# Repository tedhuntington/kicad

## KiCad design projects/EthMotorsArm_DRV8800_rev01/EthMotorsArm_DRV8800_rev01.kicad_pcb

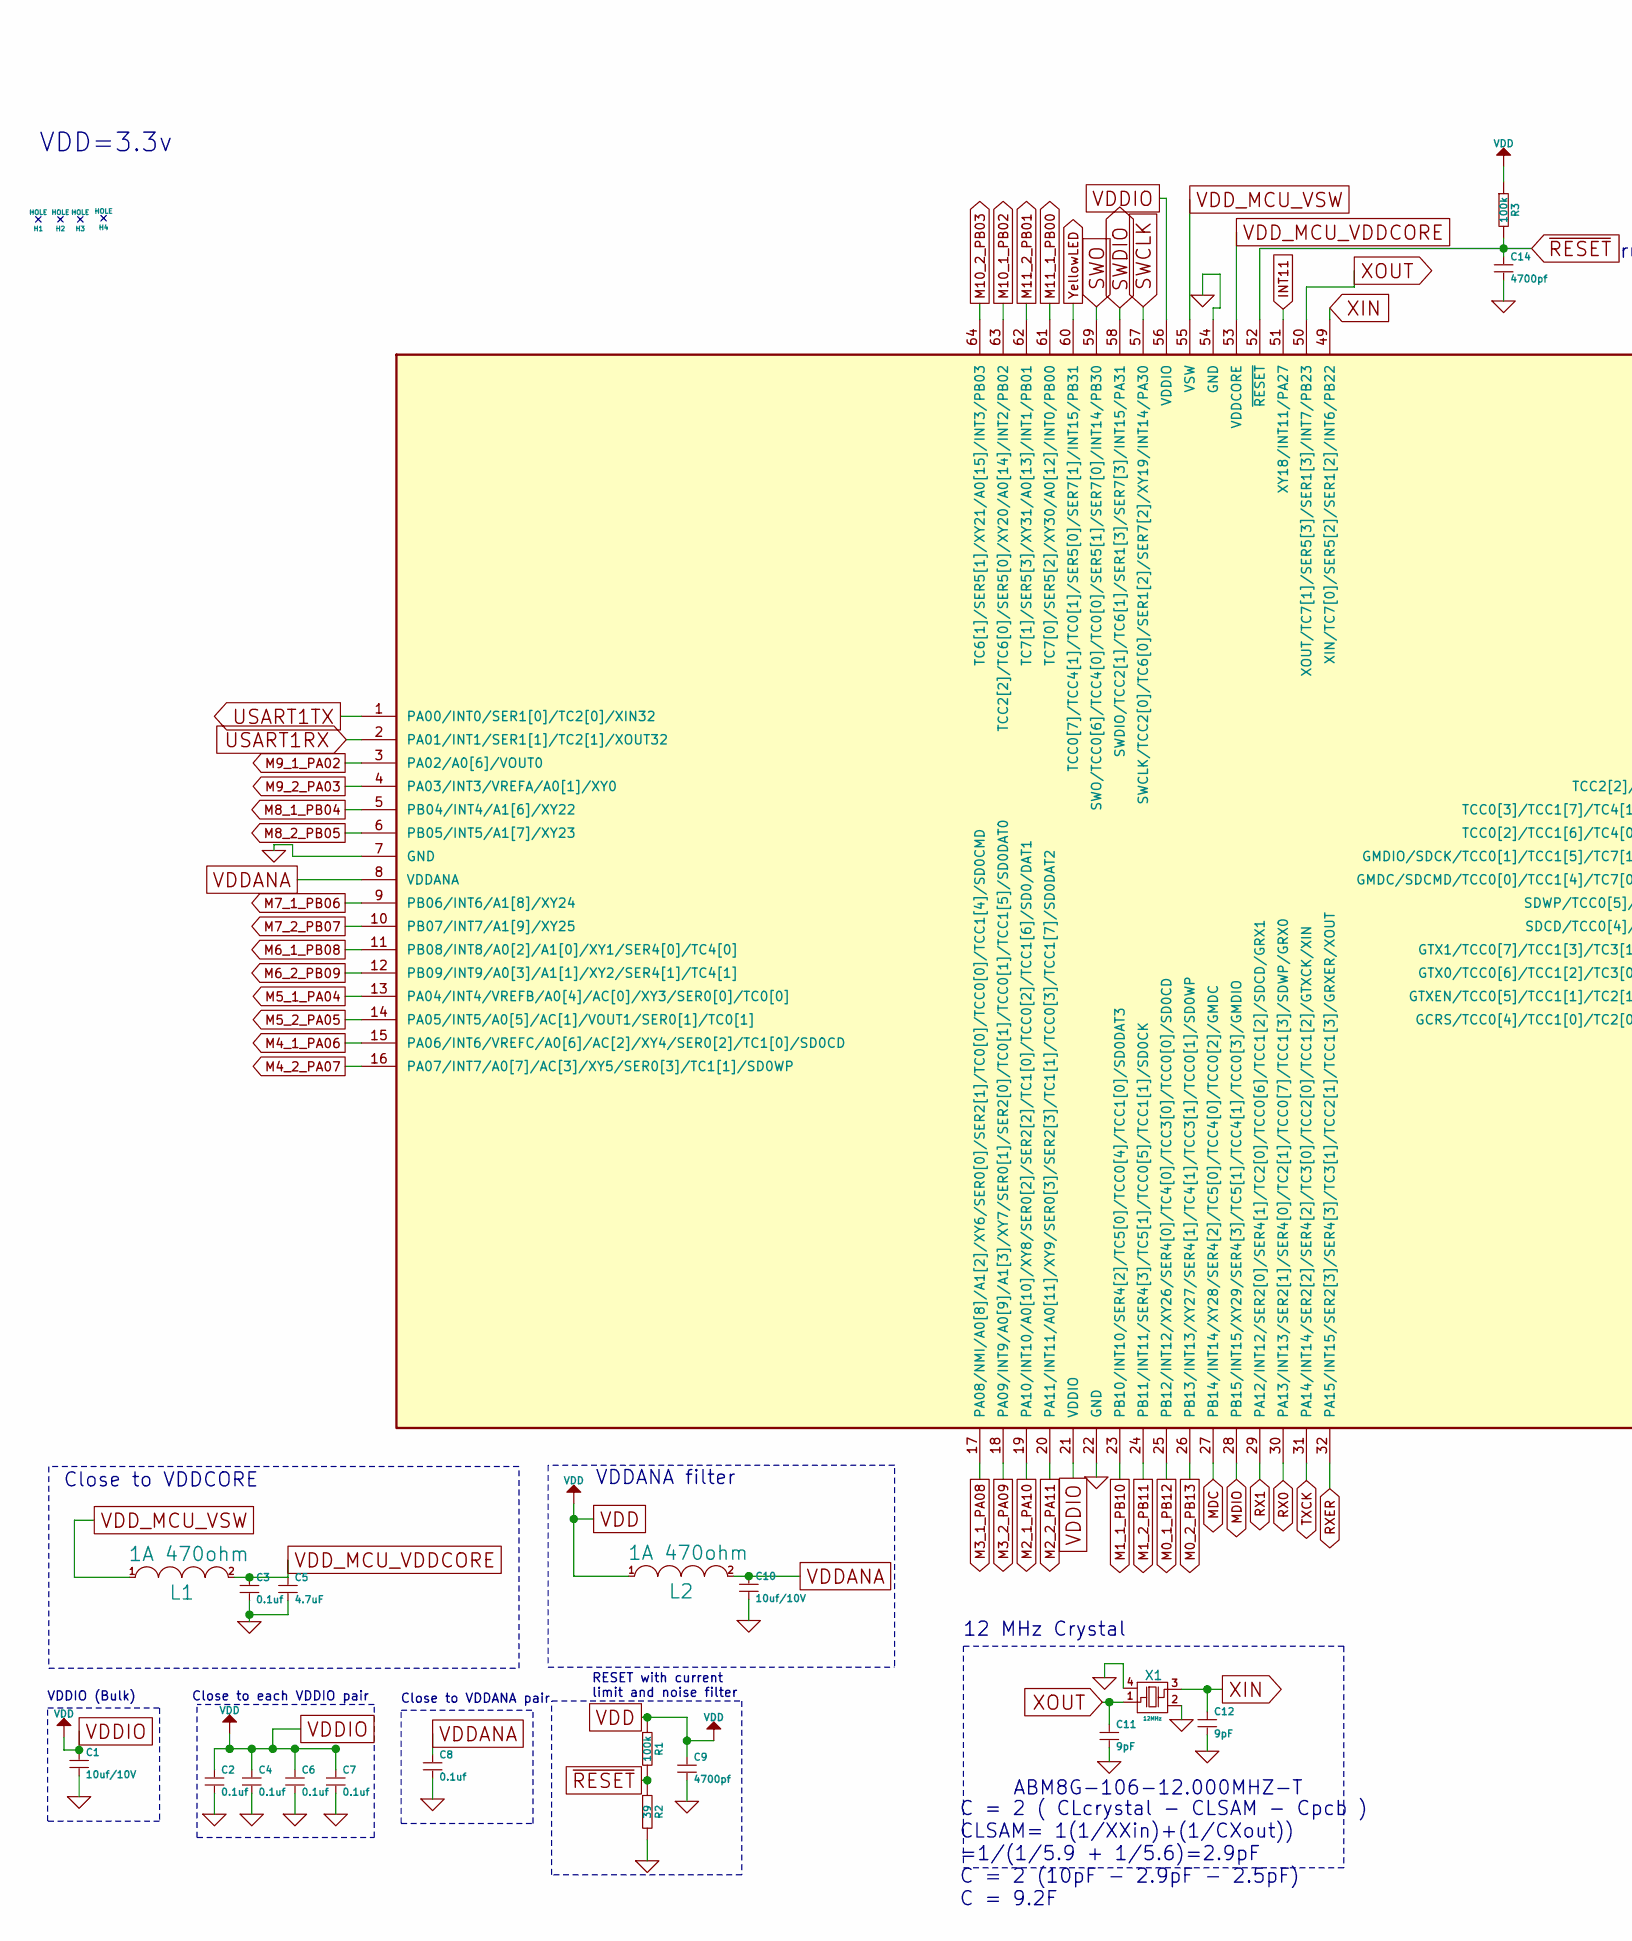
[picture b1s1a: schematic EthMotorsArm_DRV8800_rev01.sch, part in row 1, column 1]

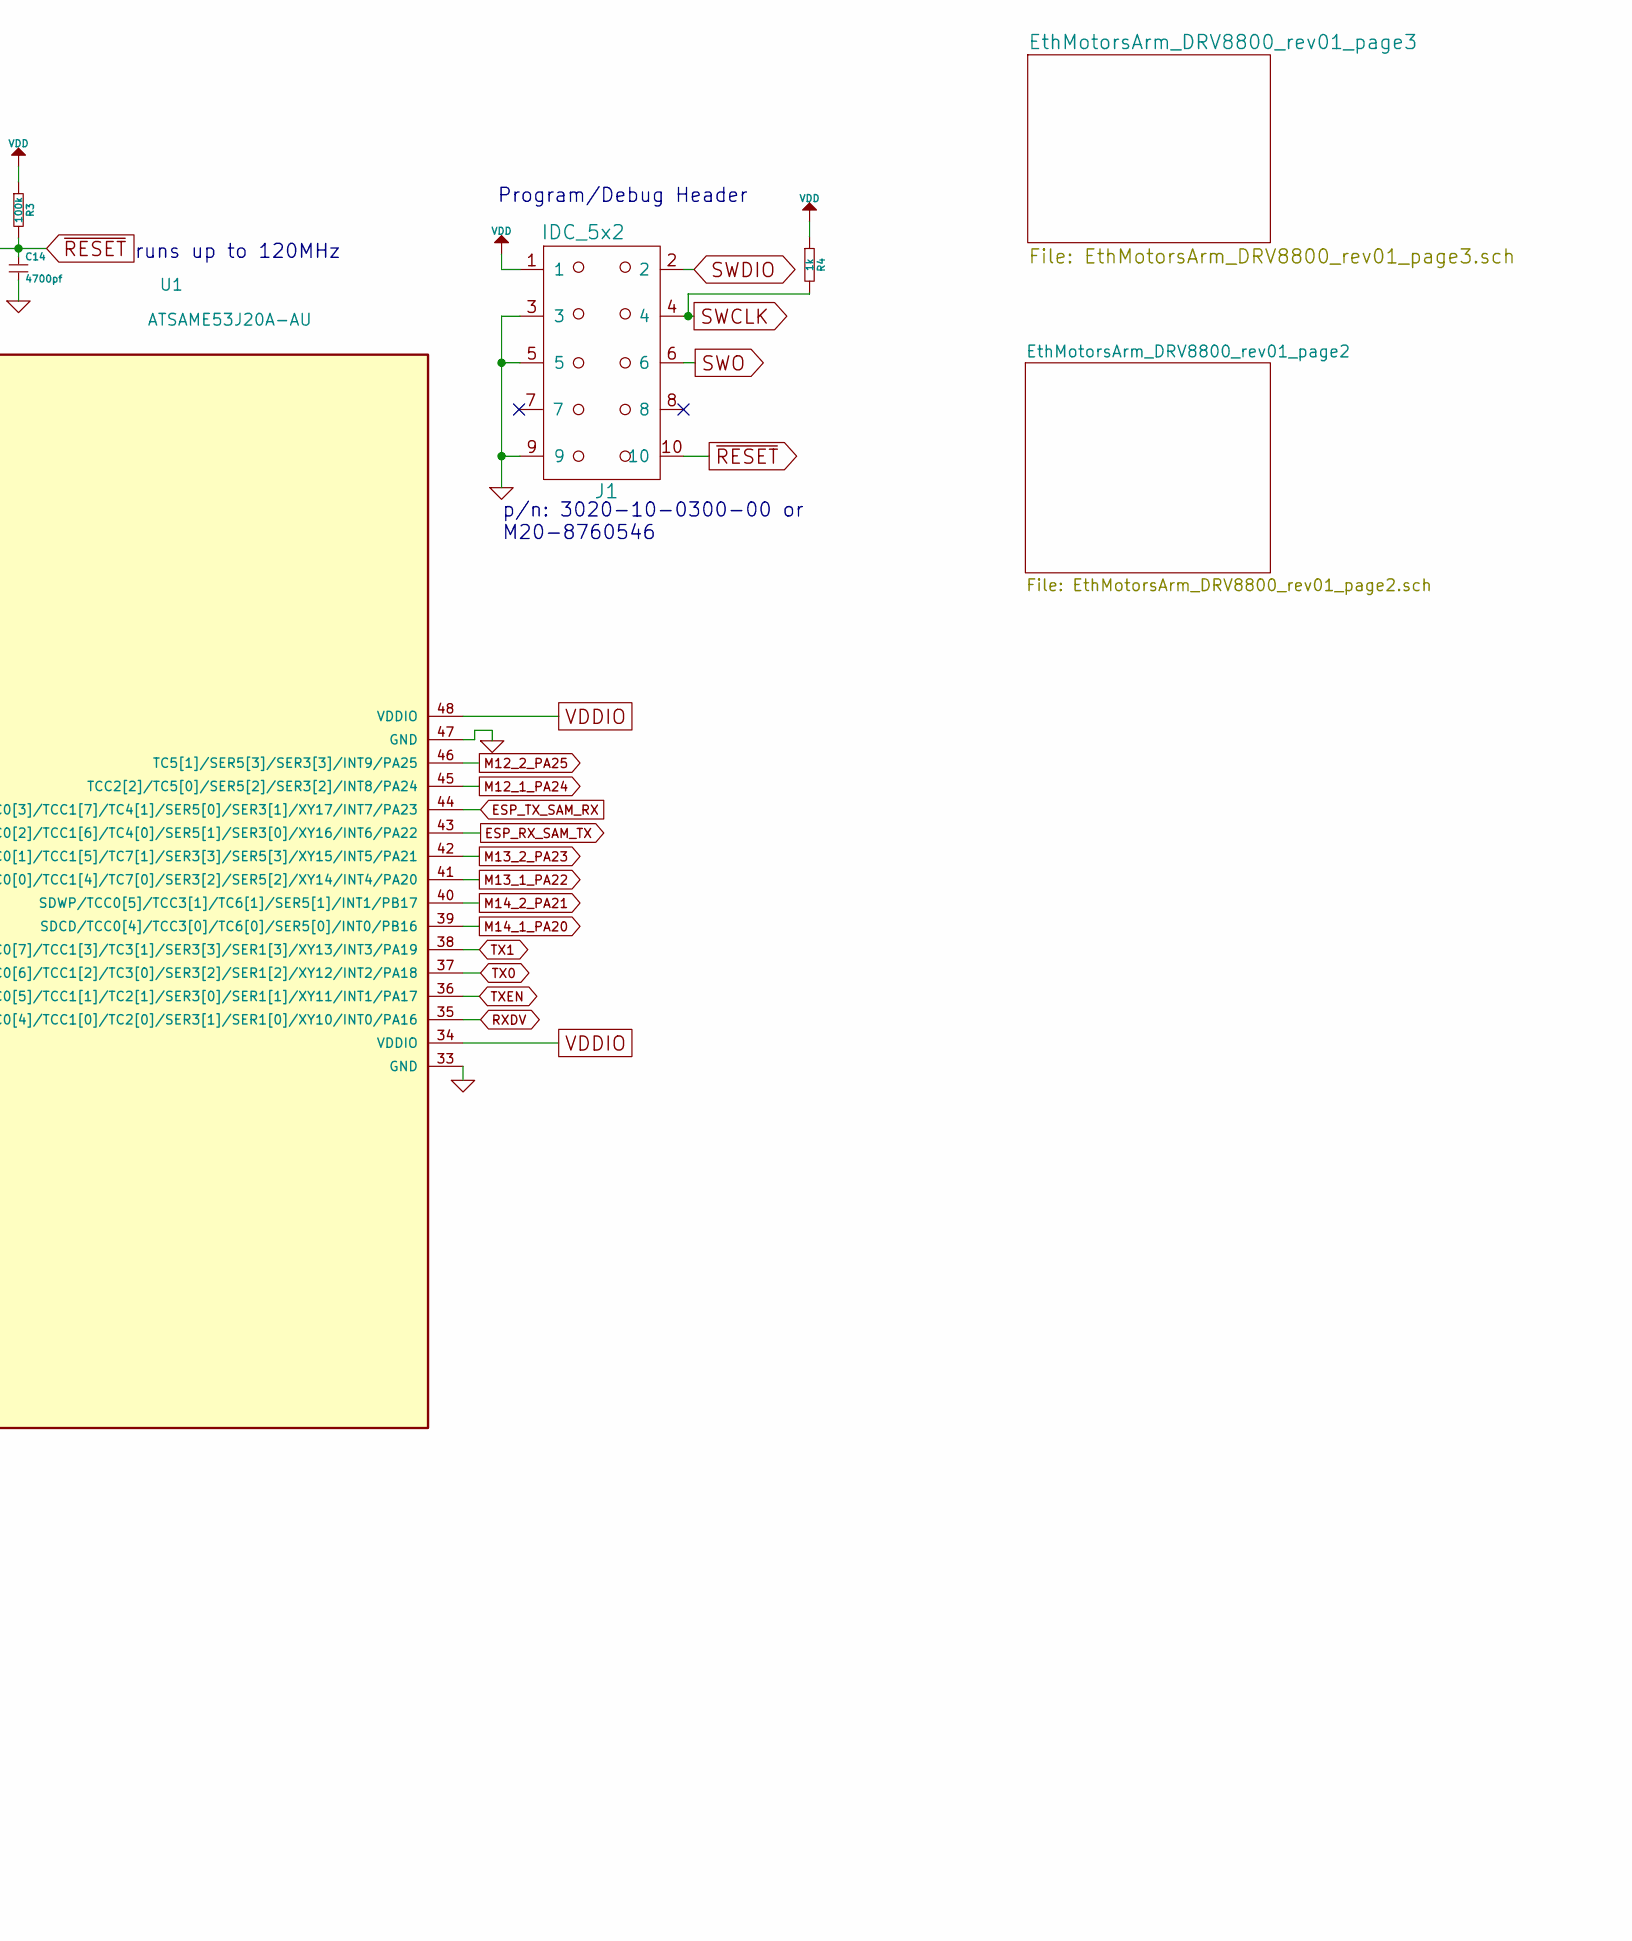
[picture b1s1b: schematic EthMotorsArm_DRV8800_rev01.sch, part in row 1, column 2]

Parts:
C1, C10: 10uf/10V; TED_SM0603_C
C2, C3, C4, C6, C7, C8: 0.1uf; TED_SM0603_C
C5: 4.7uF; TED_SM0603_C
C9, C14: 4700pf; TED_SM0603_C
C11, C12: 9pF; TED_SM0603_C
H1, H2, H3, H4: HOLE; TED_Hole_3mm
J1: IDC_5x2; TED_IDC_5x2_SMD
L1, L2: 1A 470ohm; TED_SM0603_R
R1, R3: 100k; TED_SM0603_R
R2: 39; TED_SM0603_R
R4: 1k; TED_SM0603_R
U1: ATSAME53J20A-AU; TED_TQFP64
X1: 12MHz; crystal_3.2_2.5

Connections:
ESP_RX_SAM_TX: U1.43 (TCC0[2]/TCC1[6]/TC4[0]/SER5[1]/SER3[0]/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); also elsewhere on the board
ESP_TX_SAM_RX: U1.44 (TCC0[3]/TCC1[7]/TC4[1]/SER5[0]/SER3[1]/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); also elsewhere on the board
GND: C1.2, C2.2, C3.2, C4.2, C5.2, C6.2, C7.2, C8.2, C9.2, C10.2, C11.2, C12.2, C14.2, J1.3, J1.5, J1.9, R2.2, U1.7 (GND), U1.22 (GND), U1.33 (GND), U1.47 (GND), U1.54 (GND), X1.2, X1.4; also elsewhere on the board
INT11: U1.51 (XY18/INT11/PA27); also elsewhere on the board
M0_1_PB12: U1.25 (PB12/INT12/XY26/SER4[0]/TC4[0]/TCC3[0]/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); also elsewhere on the board
M0_2_PB13: U1.26 (PB13/INT13/XY27/SER4[1]/TC4[1]/TCC3[1]/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); also elsewhere on the board
M1_1_PB10: U1.23 (PB10/INT10/SER4[2]/TC5[0]/TCC0[4]/TCC1[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); also elsewhere on the board
M1_2_PB11: U1.24 (PB11/INT11/SER4[3]/TC5[1]/TCC0[5]/TCC1[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); also elsewhere on the board
M2_1_PA10: U1.19 (PA10/INT10/A0[10]/XY8/SER0[2]/SER2[2]/T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); also elsewhere on the board
M2_2_PA11: U1.20 (PA11/INT11/A0[11]/XY9/SER0[3]/SER2[3]/T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); also elsewhere on the board
M3_1_PA08: U1.17 (PA08/NMI/A0[8]/A1[2]/XY6/SER0[0]/SER2[1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); also elsewhere on the board
M3_2_PA09: U1.18 (PA09/INT9/A0[9]/A1[3]/XY7/SER0[1]/SER2[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); also elsewhere on the board
M4_1_PA06: U1.15 (PA06/INT6/VREFC/A0[6]/AC[2]/XY4/SER0[2]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); also elsewhere on the board
M4_2_PA07: U1.16 (PA07/INT7/A0[7]/AC[3]/XY5/SER0[3]/TC1[1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); also elsewhere on the board
M5_1_PA04: U1.13 (PA04/INT4/VREFB/A0[4]/AC[0]/XY3/SER0[0]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); also elsewhere on the board
M5_2_PA05: U1.14 (PA05/INT5/A0[5]/AC[1]/VOUT1/SER0[1]/TC0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); also elsewhere on the board
M6_1_PB08: U1.11 (PB08/INT8/A0[2]/A1[0]/XY1/SER4[0]/TC4[0]); also elsewhere on the board
M6_2_PB09: U1.12 (PB09/INT9/A0[3]/A1[1]/XY2/SER4[1]/TC4[1]); also elsewhere on the board
M7_1_PB06: U1.9 (PB06/INT6/A1[8]/XY24); also elsewhere on the board
M7_2_PB07: U1.10 (PB07/INT7/A1[9]/XY25); also elsewhere on the board
M8_1_PB04: U1.5 (PB04/INT4/A1[6]/XY22); also elsewhere on the board
M8_2_PB05: U1.6 (PB05/INT5/A1[7]/XY23); also elsewhere on the board
M9_1_PA02: U1.3 (PA02/A0[6]/VOUT0); also elsewhere on the board
M9_2_PA03: U1.4 (PA03/INT3/VREFA/A0[1]/XY0); also elsewhere on the board
M10_1_PB02: U1.63 (TCC2[2]/TC6[0]/SER5[0]/XY20/A0[14]/INT2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); also elsewhere on the board
M10_2_PB03: U1.64 (TC6[1]/SER5[1]/XY21/A0[15]/INT3/PB03); also elsewhere on the board
M11_1_PB00: U1.61 (TC7[0]/SER5[2]/XY30/A0[12]/INT0/PB00); also elsewhere on the board
M11_2_PB01: U1.62 (TC7[1]/SER5[3]/XY31/A0[13]/INT1/PB01); also elsewhere on the board
M12_1_PA24: U1.45 (TCC2[2]/TC5[0]/SER5[2]/SER3[2]/INT8/PA24); also elsewhere on the board
M12_2_PA25: U1.46 (TC5[1]/SER5[3]/SER3[3]/INT9/PA25); also elsewhere on the board
M13_1_PA22: U1.41 (GMDC/SDCMD/TCC0[0]/TCC1[4]/TC7[0]/SER3[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); also elsewhere on the board
M13_2_PA23: U1.42 (GMDIO/SDCK/TCC0[1]/TCC1[5]/TC7[1]/SER3[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); also elsewhere on the board
M14_1_PA20: U1.39 (SDCD/TCC0[4]/TCC3[0]/TC6[0]/SER5[0]/INT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); also elsewhere on the board
M14_2_PA21: U1.40 (SDWP/TCC0[5]/TCC3[1]/TC6[1]/SER5[1]/INT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); also elsewhere on the board
MDC: U1.27 (PB14/INT14/XY28/SER4[2]/TC5[0]/TCC4[0]/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); also elsewhere on the board
MDIO: U1.28 (PB15/INT15/XY29/SER4[3]/TC5[1]/TCC4[1]/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); also elsewhere on the board
RX0: U1.30 (PA13/INT13/SER2[1]/SER4[0]/TC2[1]/TCC0[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); also elsewhere on the board
RX1: U1.29 (PA12/INT12/SER2[0]/SER4[1]/TC2[0]/TCC0[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); also elsewhere on the board
RXDV: U1.35 (GCRS/TCC0[4]/TCC1[0]/TC2[0]/SER3[1]/SER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); also elsewhere on the board
RXER: U1.32 (PA15/INT15/SER2[3]/SER4[3]/TC3[1]/TCC2[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); also elsewhere on the board
SWCLK: J1.4, R4.2, U1.57 (SWCLK/TCC2[0]/TC6[0]/SER1[2]/SER7[2]/XY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)
SWDIO: J1.2, U1.58 (SWDIO/TCC2[1]/TC6[1]/SER1[3]/SER7[3]/IN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)
SWO: J1.6, U1.59 (SWO/TCC0[6]/TCC4[0]/TC0[0]/SER5[1]/SER7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)
TX0: U1.37 (GTX0/TCC0[6]/TCC1[2]/TC3[0]/SER3[2]/SER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); also elsewhere on the board
TX1: U1.38 (GTX1/TCC0[7]/TCC1[3]/TC3[1]/SER3[3]/SER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); also elsewhere on the board
TXCK: U1.31 (PA14/INT14/SER2[2]/SER4[2]/TC3[0]/TCC2[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); also elsewhere on the board
TXEN: U1.36 (GTXEN/TCC0[5]/TCC1[1]/TC2[1]/SER3[0]/SE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); also elsewhere on the board
USART1RX: U1.2 (PA01/INT1/SER1[1]/TC2[1]/XOUT32); also elsewhere on the board
USART1TX: U1.1 (PA00/INT0/SER1[0]/TC2[0]/XIN32); also elsewhere on the board
VDD: C1.1, C2.1, C4.1, C6.1, C7.1, C9.1, J1.1, L2.1, R1.1, R3.1, R4.1, U1.21 (VDDIO), U1.34 (VDDIO), U1.48 (VDDIO), U1.56 (VDDIO); also elsewhere on the board
VDDANA: C8.1, C10.1, L2.2, U1.8 (VDDANA)
VDD_MCU_VDDCORE: C3.1, C5.1, L1.2, U1.53 (VDDCORE)
VDD_MCU_VSW: L1.1, U1.55 (VSW)
XIN: C12.1, U1.49 (XIN/TC7[0]/SER5[2]/SER1[2]/INT6/PB22), X1.3
XOUT: C11.1, U1.50 (XOUT/TC7[1]/SER5[3]/SER1[3]/INT7/PB23), X1.1
YellowLED: U1.60 (TCC0[7]/TCC4[1]/TC0[1]/SER5[0]/SER7[1]/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); also elsewhere on the board
~RESET~: C14.1, J1.10, R1.2, R2.1, R3.2, U1.52 (~RESET~)

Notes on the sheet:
VDD=3.3v
Close to VDDCORE
VDDANA filter
VDDIO (Bulk)
Close to each VDDIO pair
Close to VDDANA pair
RESET with current limit and noise filter
Program/Debug Header
p/n: 3020-10-0300-00 or M20-8760546
runs up to 120MHz
ABM8G-106-12.000MHZ-T
C = 2 ( CLcrystal - CLSAM - Cpcb ) CLSAM= 1(1/XXin)+(1/CXout)) =1/(1/5.9 + 1/5.6)=2.9pF C = 2 (10pF - 2.9pF - 2.5pF) C = 9.2F
12 MHz Crystal

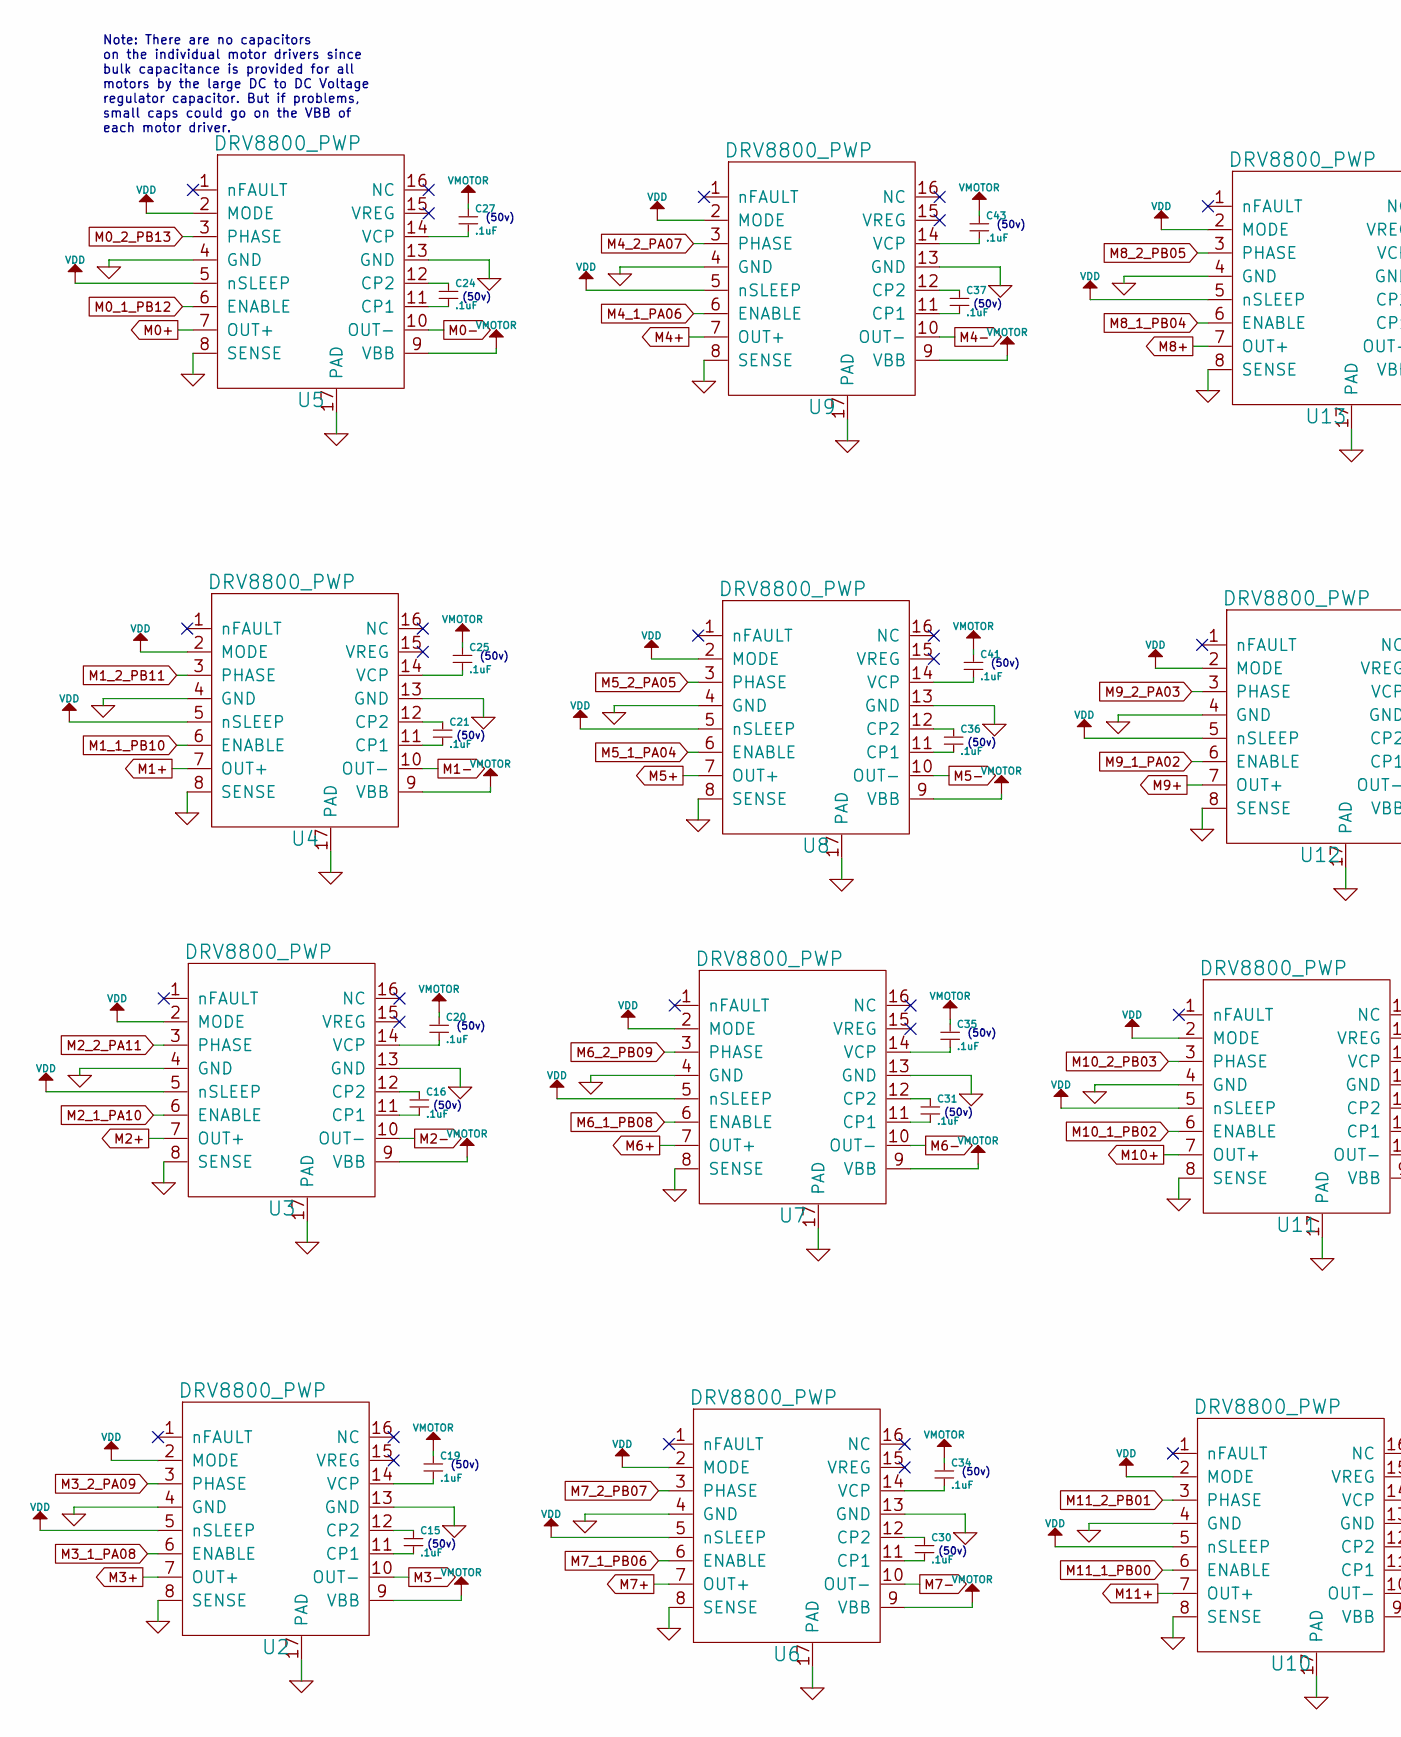
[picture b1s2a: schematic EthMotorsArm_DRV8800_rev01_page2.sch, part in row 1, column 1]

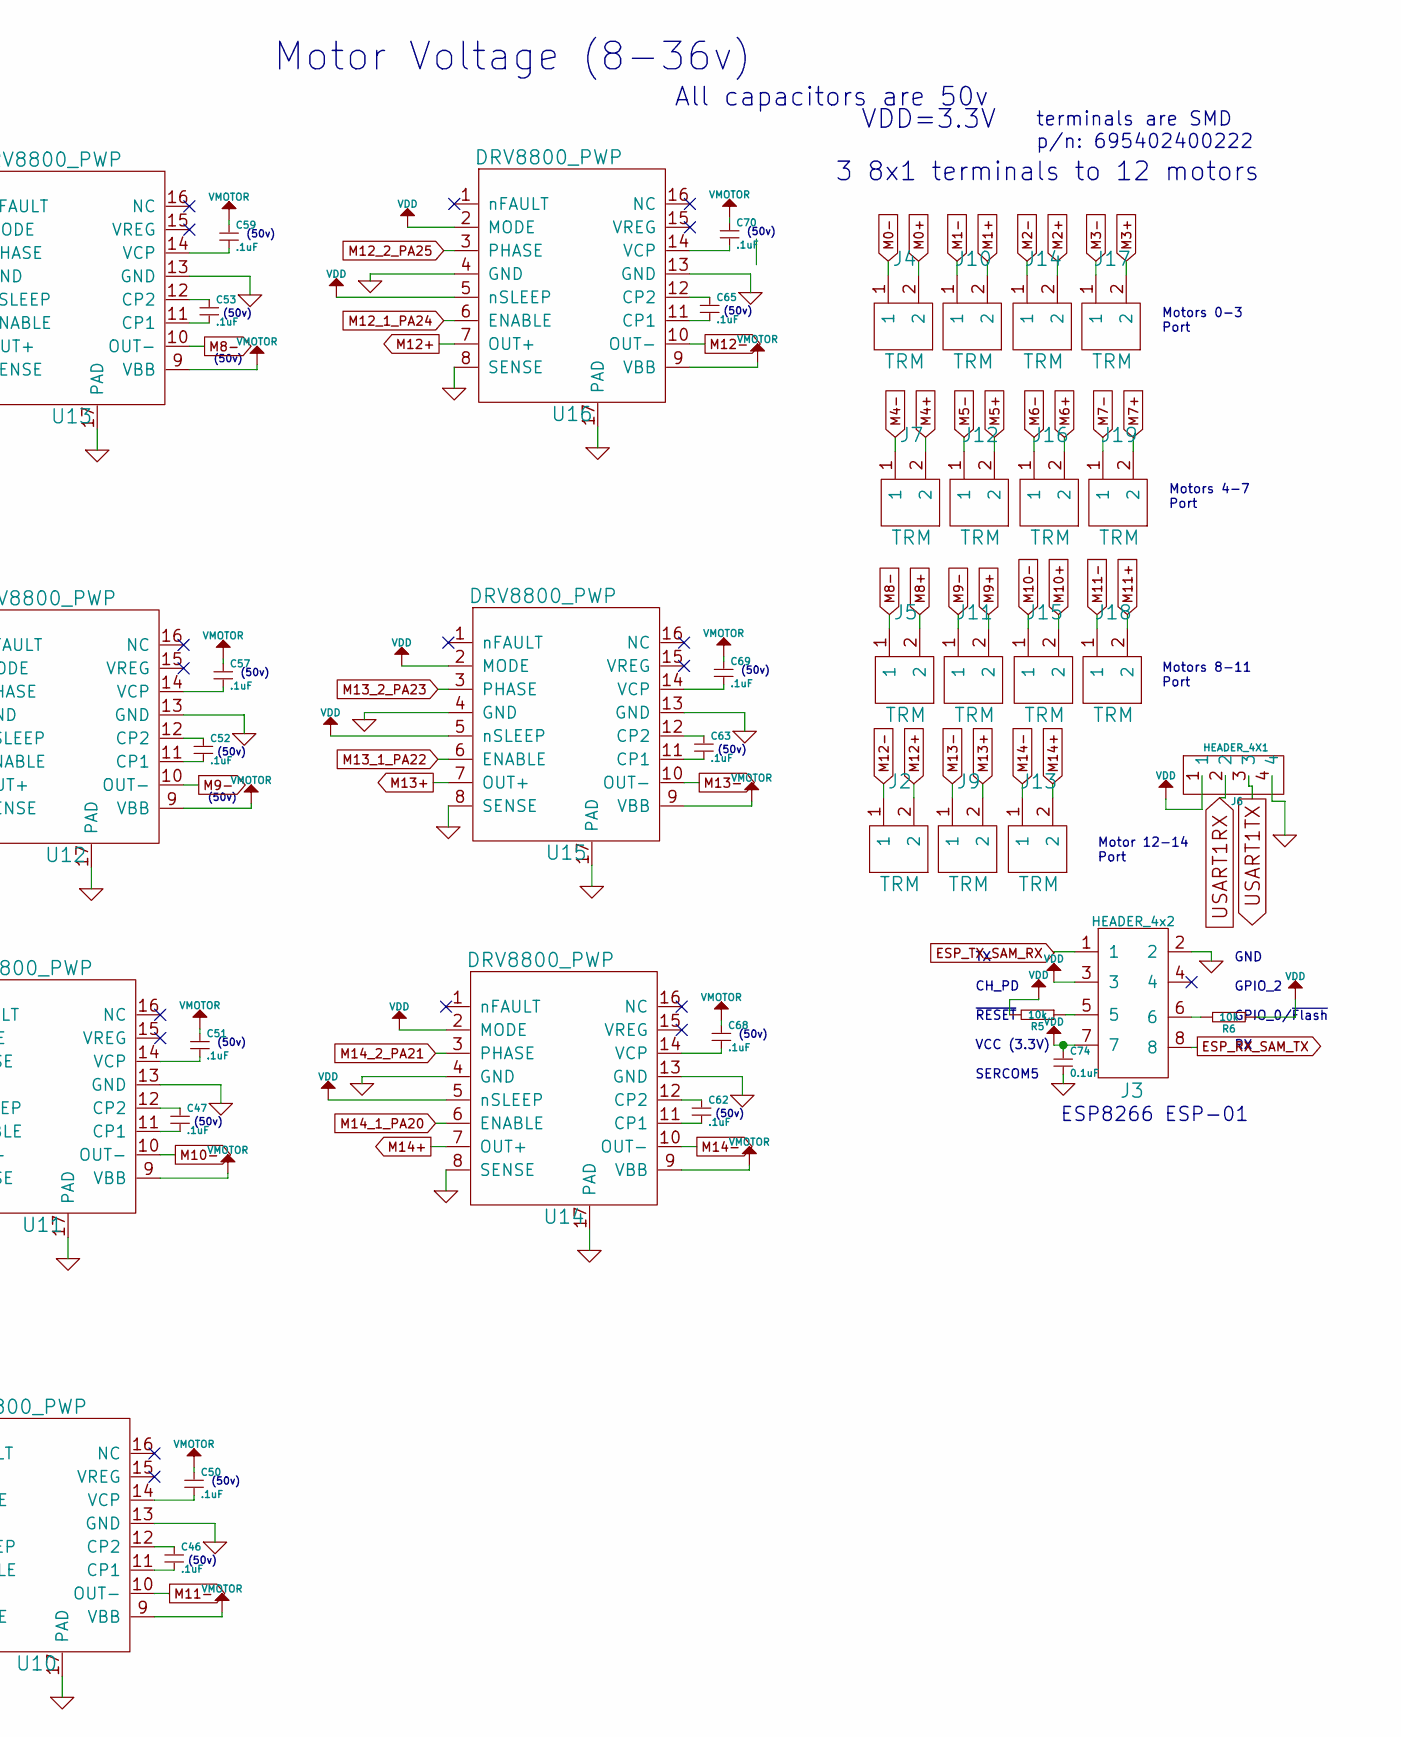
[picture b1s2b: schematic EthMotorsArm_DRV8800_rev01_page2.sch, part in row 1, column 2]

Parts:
C15, C16, C19, C20, C21, C24, C25, C27, C30, C31, C34, C35, C36, C37, C41, C43, C46, C47, C50, C51, C52, C53, C57, C59, C62, C63, C65, C68, C69, C70: .1uF; TED_SM0603_C
C74: 0.1uF; TED_SM0603_C
J2, J4, J5, J7, J9, J10, J11, J12, J13, J14, J15, J16, J17, J18, J19: TRM; TED_LED_KIND_2x1_SMD
J3: HEADER_4x2; TED_HEADER_4x2
J6: HEADER_4X1; TED_HEADER_4x1
R5, R6: 10k; TED_SM0603_R
U2, U3, U4, U5, U6, U7, U8, U9, U10, U11, U12, U13, U14, U15, U16: DRV8800_PWP; TSSOP_16+1H

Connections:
ESP_RX_SAM_TX: J3.8; also elsewhere on the board
ESP_TX_SAM_RX: J3.1; also elsewhere on the board
GND: C74.2, J3.2, J6.4, U2.4 (GND), U2.8 (SENSE), U2.13 (GND), U2.17 (PAD), U3.4 (GND), U3.8 (SENSE), U3.13 (GND), U3.17 (PAD), U4.4 (GND), U4.8 (SENSE), U4.13 (GND), U4.17 (PAD), U5.4 (GND), U5.8 (SENSE), U5.13 (GND), U5.17 (PAD), U6.4 (GND), U6.8 (SENSE), U6.13 (GND), U6.17 (PAD), U7.4 (GND), U7.8 (SENSE), U7.13 (GND), U7.17 (PAD), U8.4 (GND), U8.8 (SENSE), U8.13 (GND), U8.17 (PAD), U9.4 (GND), U9.8 (SENSE), U9.13 (GND), U9.17 (PAD), U10.4 (GND), U10.8 (SENSE), U10.13 (GND), U10.17 (PAD), U11.4 (GND), U11.8 (SENSE), U11.13 (GND), U11.17 (PAD), U12.4 (GND), U12.8 (SENSE), U12.13 (GND), U12.17 (PAD), U13.4 (GND), U13.8 (SENSE), U13.13 (GND), U13.17 (PAD), U14.4 (GND), U14.8 (SENSE), U14.13 (GND), U14.17 (PAD), U15.4 (GND), U15.8 (SENSE), U15.13 (GND), U15.17 (PAD), U16.4 (GND), U16.8 (SENSE), U16.13 (GND), U16.17 (PAD); also elsewhere on the board
M0+: J4.2, U5.7 (OUT+)
M0-: J4.1, U5.10 (OUT-)
M0_1_PB12: U5.6 (ENABLE); also elsewhere on the board
M0_2_PB13: U5.3 (PHASE); also elsewhere on the board
M1+: J10.2, U4.7 (OUT+)
M1-: J10.1, U4.10 (OUT-)
M1_1_PB10: U4.6 (ENABLE); also elsewhere on the board
M1_2_PB11: U4.3 (PHASE); also elsewhere on the board
M2+: J14.2, U3.7 (OUT+)
M2-: J14.1, U3.10 (OUT-)
M2_1_PA10: U3.6 (ENABLE); also elsewhere on the board
M2_2_PA11: U3.3 (PHASE); also elsewhere on the board
M3+: J17.2, U2.7 (OUT+)
M3-: J17.1, U2.10 (OUT-)
M3_1_PA08: U2.6 (ENABLE); also elsewhere on the board
M3_2_PA09: U2.3 (PHASE); also elsewhere on the board
M4+: J7.2, U9.7 (OUT+)
M4-: J7.1, U9.10 (OUT-)
M4_1_PA06: U9.6 (ENABLE); also elsewhere on the board
M4_2_PA07: U9.3 (PHASE); also elsewhere on the board
M5+: J12.2, U8.7 (OUT+)
M5-: J12.1, U8.10 (OUT-)
M5_1_PA04: U8.6 (ENABLE); also elsewhere on the board
M5_2_PA05: U8.3 (PHASE); also elsewhere on the board
M6+: J16.2, U7.7 (OUT+)
M6-: J16.1, U7.10 (OUT-)
M6_1_PB08: U7.6 (ENABLE); also elsewhere on the board
M6_2_PB09: U7.3 (PHASE); also elsewhere on the board
M7+: J19.2, U6.7 (OUT+)
M7-: J19.1, U6.10 (OUT-)
M7_1_PB06: U6.6 (ENABLE); also elsewhere on the board
M7_2_PB07: U6.3 (PHASE); also elsewhere on the board
M8+: J5.2, U13.7 (OUT+)
M8-: J5.1, U13.10 (OUT-)
M8_1_PB04: U13.6 (ENABLE); also elsewhere on the board
M8_2_PB05: U13.3 (PHASE); also elsewhere on the board
M9+: J11.2, U12.7 (OUT+)
M9-: J11.1, U12.10 (OUT-)
M9_1_PA02: U12.6 (ENABLE); also elsewhere on the board
M9_2_PA03: U12.3 (PHASE); also elsewhere on the board
M10+: J15.2, U11.7 (OUT+)
M10-: J15.1, U11.10 (OUT-)
M10_1_PB02: U11.6 (ENABLE); also elsewhere on the board
M10_2_PB03: U11.3 (PHASE); also elsewhere on the board
M11+: J18.2, U10.7 (OUT+)
M11-: J18.1, U10.10 (OUT-)
M11_1_PB00: U10.6 (ENABLE); also elsewhere on the board
M11_2_PB01: U10.3 (PHASE); also elsewhere on the board
M12+: J2.2, U16.7 (OUT+)
M12-: J2.1, U16.10 (OUT-)
M12_1_PA24: U16.6 (ENABLE); also elsewhere on the board
M12_2_PA25: U16.3 (PHASE); also elsewhere on the board
M13+: J9.2, U15.7 (OUT+)
M13-: J9.1, U15.10 (OUT-)
M13_1_PA22: U15.6 (ENABLE); also elsewhere on the board
M13_2_PA23: U15.3 (PHASE); also elsewhere on the board
M14+: J13.2, U14.7 (OUT+)
M14-: J13.1, U14.10 (OUT-)
M14_1_PA20: U14.6 (ENABLE); also elsewhere on the board
M14_2_PA21: U14.3 (PHASE); also elsewhere on the board
unnamed: C15.1, U2.12 (CP2)
unnamed: C15.2, U2.11 (CP1)
unnamed: C16.1, U3.12 (CP2)
unnamed: C16.2, U3.11 (CP1)
unnamed: C19.2, U2.14 (VCP)
unnamed: C20.2, U3.14 (VCP)
unnamed: C21.1, U4.12 (CP2)
unnamed: C21.2, U4.11 (CP1)
unnamed: C24.1, U5.12 (CP2)
unnamed: C24.2, U5.11 (CP1)
unnamed: C25.2, U4.14 (VCP)
unnamed: C27.2, U5.14 (VCP)
unnamed: C30.1, U6.12 (CP2)
unnamed: C30.2, U6.11 (CP1)
unnamed: C31.1, U7.12 (CP2)
unnamed: C31.2, U7.11 (CP1)
unnamed: C34.2, U6.14 (VCP)
unnamed: C35.2, U7.14 (VCP)
unnamed: C36.1, U8.12 (CP2)
unnamed: C36.2, U8.11 (CP1)
unnamed: C37.1, U9.12 (CP2)
unnamed: C37.2, U9.11 (CP1)
unnamed: C41.2, U8.14 (VCP)
unnamed: C43.2, U9.14 (VCP)
unnamed: C46.1, U10.12 (CP2)
unnamed: C46.2, U10.11 (CP1)
unnamed: C47.1, U11.12 (CP2)
unnamed: C47.2, U11.11 (CP1)
unnamed: C50.2, U10.14 (VCP)
unnamed: C51.2, U11.14 (VCP)
unnamed: C52.1, U12.12 (CP2)
unnamed: C52.2, U12.11 (CP1)
unnamed: C53.1, U13.12 (CP2)
unnamed: C53.2, U13.11 (CP1)
unnamed: C57.2, U12.14 (VCP)
unnamed: C59.2, U13.14 (VCP)
unnamed: C62.1, U14.12 (CP2)
unnamed: C62.2, U14.11 (CP1)
unnamed: C63.1, U15.12 (CP2)
unnamed: C63.2, U15.11 (CP1)
unnamed: C65.1, U16.12 (CP2)
unnamed: C65.2, U16.11 (CP1)
unnamed: C68.2, U14.14 (VCP)
unnamed: C69.2, U15.14 (VCP)
unnamed: C70.2, U16.14 (VCP)
unnamed: J3.5, R5.1
unnamed: J3.6, R6.2
USART1RX: J6.2; also elsewhere on the board
USART1TX: J6.3; also elsewhere on the board
VDD: C74.1, J3.3, J3.7, J6.1, R5.2, R6.1, U2.2 (MODE), U2.5 (nSLEEP), U3.2 (MODE), U3.5 (nSLEEP), U4.2 (MODE), U4.5 (nSLEEP), U5.2 (MODE), U5.5 (nSLEEP), U6.2 (MODE), U6.5 (nSLEEP), U7.2 (MODE), U7.5 (nSLEEP), U8.2 (MODE), U8.5 (nSLEEP), U9.2 (MODE), U9.5 (nSLEEP), U10.2 (MODE), U10.5 (nSLEEP), U11.2 (MODE), U11.5 (nSLEEP), U12.2 (MODE), U12.5 (nSLEEP), U13.2 (MODE), U13.5 (nSLEEP), U14.2 (MODE), U14.5 (nSLEEP), U15.2 (MODE), U15.5 (nSLEEP), U16.2 (MODE), U16.5 (nSLEEP); also elsewhere on the board
VMotor: C19.1, C20.1, C25.1, C27.1, C34.1, C35.1, C41.1, C43.1, C50.1, C51.1, C57.1, C59.1, C68.1, C69.1, C70.1, U2.9 (VBB), U3.9 (VBB), U4.9 (VBB), U5.9 (VBB), U6.9 (VBB), U7.9 (VBB), U8.9 (VBB), U9.9 (VBB), U10.9 (VBB), U11.9 (VBB), U12.9 (VBB), U13.9 (VBB), U14.9 (VBB), U15.9 (VBB), U16.9 (VBB); also elsewhere on the board

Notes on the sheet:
3 8x1 terminals to 12 motors
Motors 0-3 Port
Motor Voltage (8-36v)
Motors 4-7 Port
Motors 8-11 Port
VDD=3.3V
All capacitors are 50v
Motor 12-14 Port
ESP8266 ESP-01
TX CH_PD ~RESET~ VCC (3.3V) SERCOM5
GND GPIO_2 GPIO_0/~Flash~ RX
(50v)
Note: There are no capacitors on the individual motor drivers since bulk capacitance is provided for all motors by the large DC to DC Voltage regulator capacitor. But if problems, small caps could go on the VBB of each motor driver.
terminals are SMD p/n: 695402400222

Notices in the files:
projects/EthMotors_DRV8800_rev02/EthMotors_DRV8800_rev02.kicad_pcb:
GPL License
